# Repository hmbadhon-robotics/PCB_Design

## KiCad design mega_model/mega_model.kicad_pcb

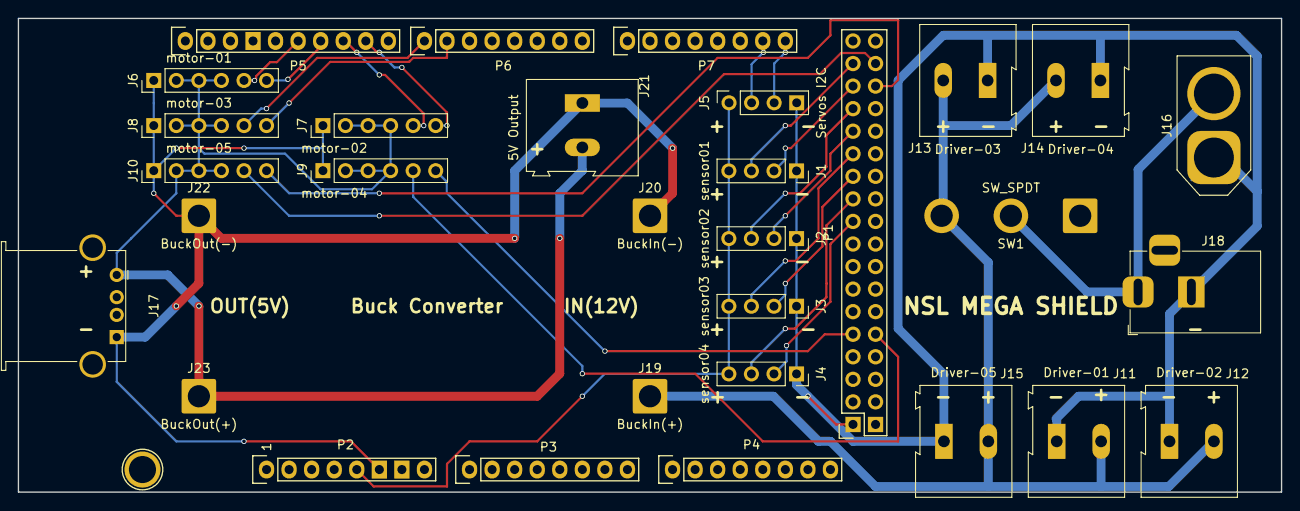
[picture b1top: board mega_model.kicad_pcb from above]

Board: 2 copper layers, 142.2 x 53.3 mm, 32 parts (0 on the bottom side), 25 nets.

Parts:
J1: sensor01; PinSocket_1x04_P2.54mm_Vertical
J2: sensor02; PinSocket_1x04_P2.54mm_Vertical
J3: sensor03; PinSocket_1x04_P2.54mm_Vertical
J4: sensor04; PinSocket_1x04_P2.54mm_Vertical
J5: Servos I2C; PinSocket_1x04_P2.54mm_Vertical
J6: motor-01; PinHeader_1x06_P2.54mm_Vertical
J7: motor-02; PinHeader_1x06_P2.54mm_Vertical
J8: motor-03; PinHeader_1x06_P2.54mm_Vertical
J9: motor-04; PinHeader_1x06_P2.54mm_Vertical
J10: motor-05; PinHeader_1x06_P2.54mm_Vertical
J11: Driver-01; TerminalBlock_Altech_AK300-2_P5.00mm
J12: Driver-02; TerminalBlock_Altech_AK300-2_P5.00mm
J13: Driver-03; TerminalBlock_Altech_AK300-2_P5.00mm
J14: Driver-04; TerminalBlock_Altech_AK300-2_P5.00mm
J15: Driver-05; TerminalBlock_Altech_AK300-2_P5.00mm
J16: Power; AMASS_XT60-M_1x02_P7.20mm_Vertical
J17: USB_A; USB_A_Stewart_SS-52100-001_Horizontal
J18: Barrel_Jack; BarrelJack_Horizontal
J19: BuckIn(+); SolderWire-2sqmm_1x01_D2mm_OD3.9mm
J20: BuckIn(-); SolderWire-2sqmm_1x01_D2mm_OD3.9mm
J21: 5V Output; TerminalBlock_Altech_AK300-2_P5.00mm
J22: BuckOut(-); SolderWire-2sqmm_1x01_D2mm_OD3.9mm
J23: BuckOut(+); SolderWire-2sqmm_1x01_D2mm_OD3.9mm
P1: Digital; Socket_Strip_Arduino_2x18
P2: Power; Socket_Strip_Arduino_1x08
P3, P4: Analog; Socket_Strip_Arduino_1x08
P5: PWM; Socket_Strip_Arduino_1x10
P6: PWM; Socket_Strip_Arduino_1x08
P7: Communication; Socket_Strip_Arduino_1x08
P8: CONN_01X01; Arduino_1pin
SW1: SW_SPDT; SolderWire-2sqmm_1x03_P7.8mm_D2mm_OD3.9mm

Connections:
+5V: J1.4, J2.4, J3.4, J4.4, J5.1, P1.35, P1.36, P2.5
+5VA: J6.2, J6.3, J6.4, J7.2, J7.3, J7.4, J8.2, J8.3, J8.4, J9.2, J9.3, J9.4, J10.2, J10.3, J10.4, J17.1 (VBUS), J21.2, J23.1
+12V: J16.2, J18.1, SW1.2 (B)
+12VA: J11.1, J12.1, J13.1, J14.1, J15.1, J19.1, SW1.3 (C)
/6(**): J8.6, P6.2
/7(**): J8.5, P6.1
/9(**): J7.6, P5.9
/10(**): J7.5, P5.8
/11(**): J6.6, P5.7
/12(**): J6.5, P5.6
/20(SDA): J5.2, P5.2, P7.7
/21(SCL): J5.3, P5.1, P7.8
/22: J1.3, P1.33
/23: J10.5, P1.34
/24: J1.2, P1.31
/25: J10.6, P1.32
/26: J2.3, P1.29
/28: J2.2, P1.27
/30: J3.3, P1.25
/32: J3.2, P1.23
/34: J4.3, P1.21
/36: J4.2, P1.19
/46: J9.6, P1.9
/47: J9.5, P1.10
GND: J1.1, J2.1, J3.1, J4.1, J5.4, J6.1, J7.1, J8.1, J9.1, J10.1, J11.2, J12.2, J13.2, J14.2, J15.2, J16.1, J17.4 (GND), J18.2, J20.1, J21.1, J22.1, P1.1, P1.2, P2.6, P2.7, P5.4
